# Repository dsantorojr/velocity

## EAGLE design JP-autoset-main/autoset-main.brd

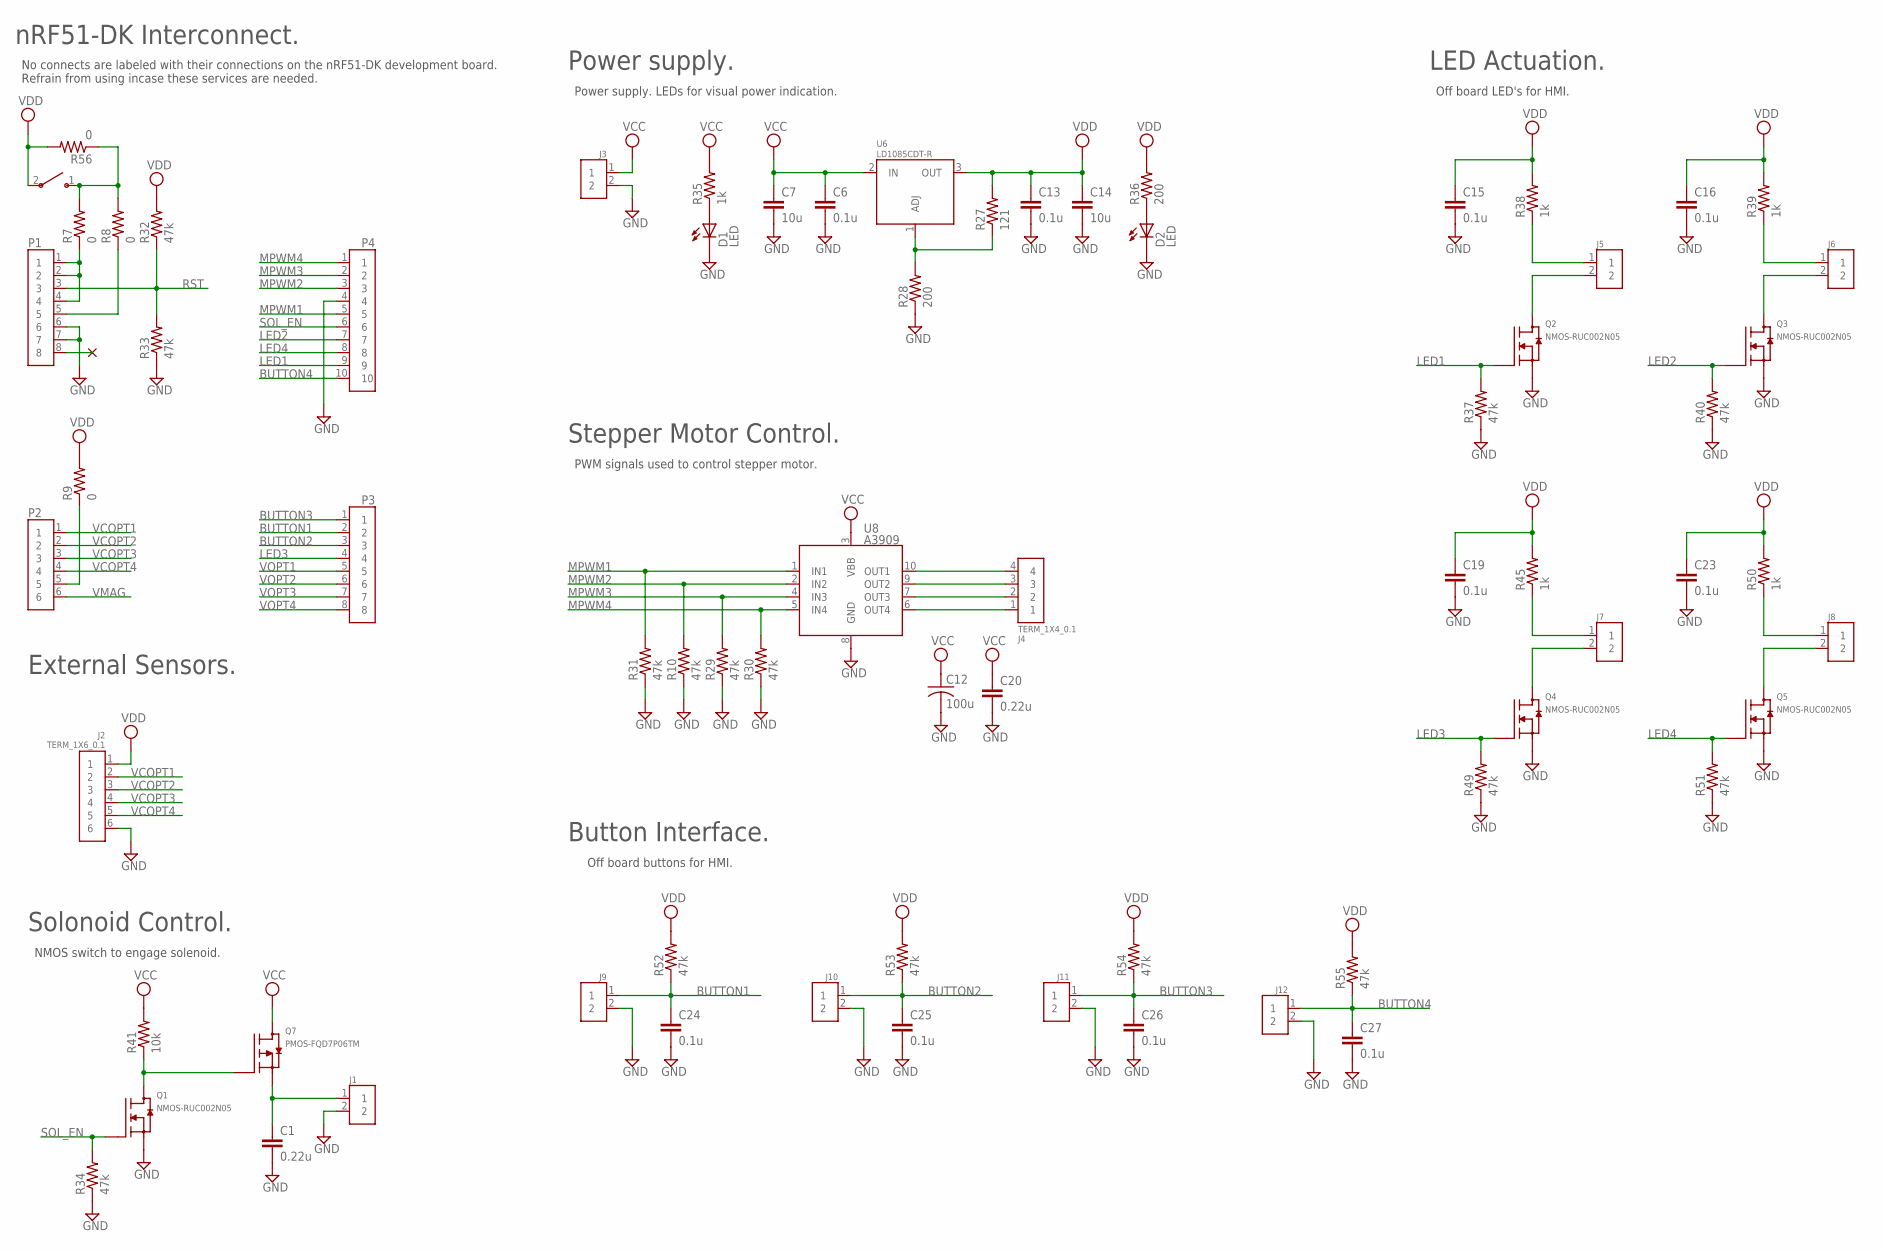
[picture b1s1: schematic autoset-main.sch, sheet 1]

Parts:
C1, C20: 0.22u; C0603
C6, C13, C15, C16, C19, C23, C24, C25, C26, C27: 0.1u; C0603
C7, C14: 10u; C0603
C12: 100u; CPOL-3.5MM
D1, D2: LED; L0805
J1, J3, J5, J6, J7, J8, J9, J10, J11, J12: TERM_1X2_0.1
J2: TERM_1X6_0.1
J4: TERM_1X4_0.1
P1, P3: RECT_1X8; RECT_1X8_0.1
P2: RECT_1X6; RECT_1X6_0.1
P4: RECT_1X10; RECT_1X10_0.1
Q1, Q2, Q3, Q4, Q5: NMOS-RUC002N05; SOT23
Q7: PMOS-FQD7P06TM; TO252
R7, R8, R9, R56: 0; R0603
R10, R29, R30, R31, R32, R33, R34, R37, R40, R49, R51, R52, R53, R54, R55: 47k; R0603
R27: 121; R0603
R28, R36: 200; R0603
R35, R38, R39, R45, R50: 1k; R0603
R41: 10k; R0603
SW1: GPTS203211B
U6: LD1085CDT-R; TO252
U8: A3909; SSOP10
Z15: NC; NC_TH

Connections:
BUTTON1: C24.1, J9.1, P3.2, R52.1
BUTTON2: C25.1, J10.1, P3.3, R53.1
BUTTON3: C26.1, J11.1, P3.1, R54.1
BUTTON4: C27.1, J12.1, P4.10, R55.1
GND: C1.2, C6.2, C7.2, C12.P$2 (2), C13.2, C14.2, C15.2, C16.2, C19.2, C20.2, C23.2, C24.2, C25.2, C26.2, C27.2, D1.2 (C), D2.2 (C), J1.2, J2.6, J3.2, J9.2, J10.2, J11.2, J12.2, P1.6, P1.7, P4.4, Q1.1 (S), Q2.1 (S), Q3.1 (S), Q4.1 (S), Q5.1 (S), R10.1, R28.1, R29.1, R30.1, R31.1, R33.1, R34.1, R37.1, R40.1, R49.1, R51.1, U8.8 (GND); also elsewhere on the board
LED1: P4.9, Q2.2 (G), R37.2
LED2: P4.7, Q3.2 (G), R40.2
LED3: P3.4, Q4.2 (G), R49.2
LED4: P4.8, Q5.2 (G), R51.2
MPWM1: P4.5, R31.2, U8.1 (IN1)
MPWM2: P4.3, R10.2, U8.2 (IN2)
MPWM3: P4.2, R29.2, U8.4 (IN3)
MPWM4: P4.1, R30.2, U8.5 (IN4)
unnamed: P1.8, Z15.P$1
unnamed: J6.2, Q3.3 (D)
unnamed: R7.2, R8.2, R56.1, SW1.1
unnamed: P1.1, P1.2, P1.4, R7.1
unnamed: J4.4, U8.10 (OUT1)
unnamed: R27.1, R28.2, U6.1 (ADJ)
unnamed: J4.3, U8.9 (OUT2)
unnamed: J5.2, Q2.3 (D)
unnamed: J5.1, R38.1
unnamed: J6.1, R39.1
unnamed: J7.2, Q4.3 (D)
unnamed: J7.1, R45.1
unnamed: J8.2, Q5.3 (D)
unnamed: J4.2, U8.7 (OUT3)
unnamed: J4.1, U8.6 (OUT4)
unnamed: J8.1, R50.1
unnamed: P2.5, R9.1
unnamed: C1.1, J1.1, Q7.3 (D)
unnamed: P1.5, R8.1
unnamed: Q1.3 (D), Q7.1 (G), R41.1
unnamed: D1.1 (A), R35.1
unnamed: D2.1 (A), R36.1
RST: P1.3, R32.1, R33.2
SOL_EN: P4.6, Q1.2 (G), R34.2
VCC: C6.1, C7.1, C12.P$1 (1), C20.1, J3.1, Q7.2 (S), R35.2, R41.2, U6.2 (IN), U8.3 (VBB)
VCOPT1: J2.2, P2.1
VCOPT2: J2.3, P2.2
VCOPT3: J2.4, P2.3
VCOPT4: J2.5, P2.4
VDD: C13.1, C14.1, C15.1, C16.1, C19.1, C23.1, J2.1, R9.2, R27.2, R32.2, R36.2, R38.2, R39.2, R45.2, R50.2, R52.2, R53.2, R54.2, R55.2, R56.2, SW1.2, U6.3 (OUT); also elsewhere on the board
VMAG: P2.6; also elsewhere on the board
VOPT1: P3.5; also elsewhere on the board
VOPT2: P3.6; also elsewhere on the board
VOPT3: P3.7; also elsewhere on the board
VOPT4: P3.8; also elsewhere on the board

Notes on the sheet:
nRF51-DK Interconnect.
No connects are labeled with their connections on the nRF51-DK development board. Refrain from using incase these services are needed.
Power supply.
Power supply. LEDs for visual power indication.
Solonoid Control.
NMOS switch to engage solenoid.
Stepper Motor Control.
PWM signals used to control stepper motor.
External Sensors.
LED Actuation.
Off board LED's for HMI.
Button Interface.
Off board buttons for HMI.

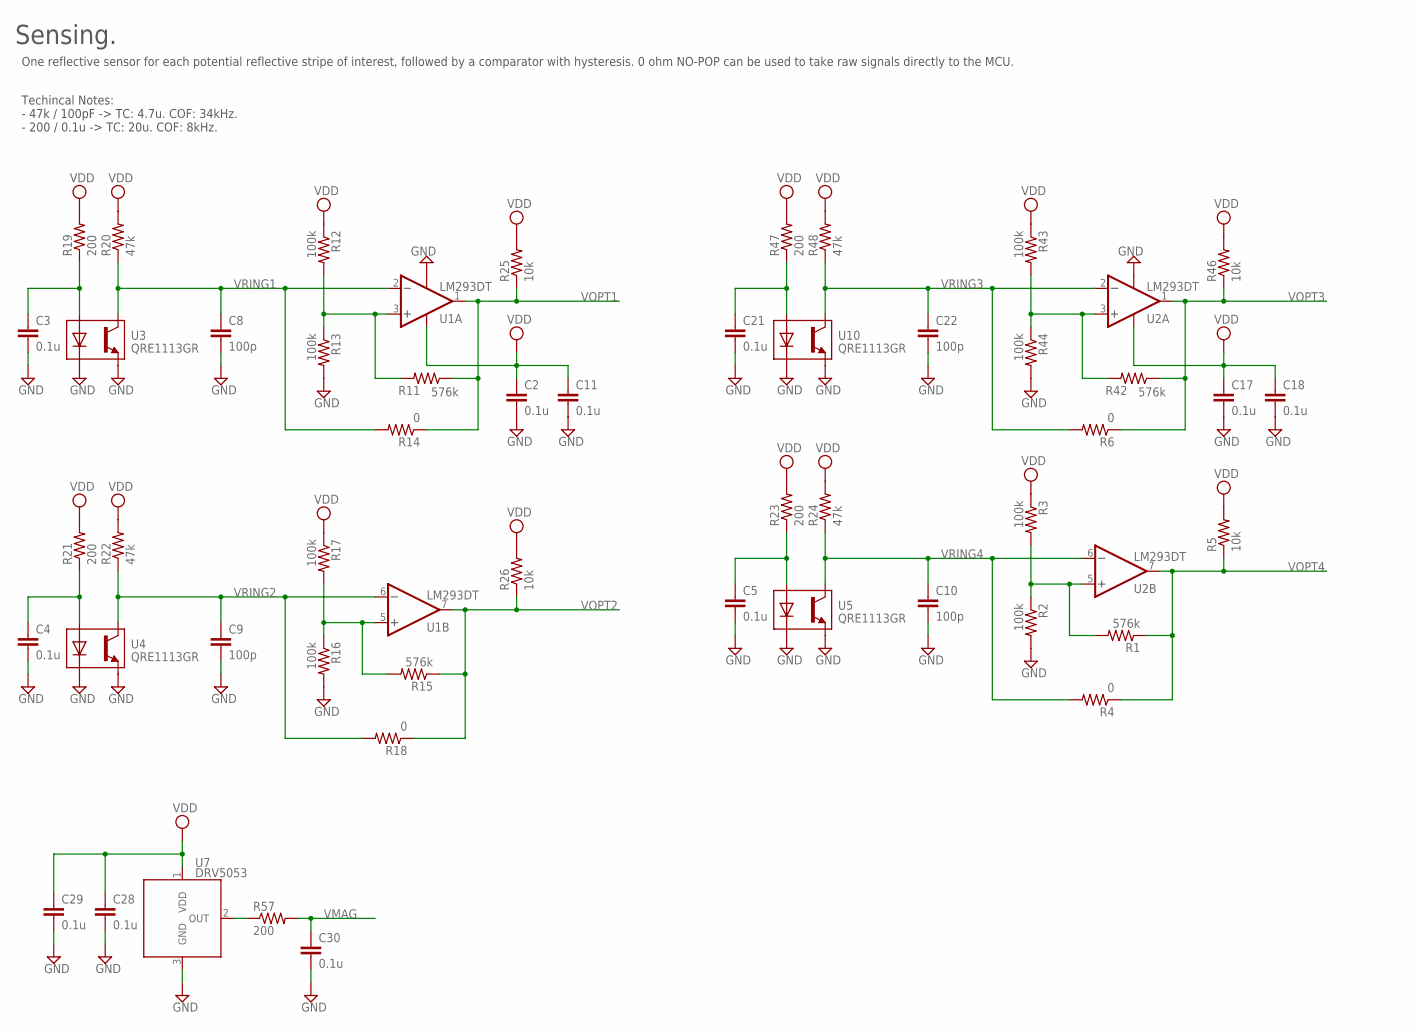
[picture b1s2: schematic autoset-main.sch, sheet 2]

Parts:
C2, C3, C4, C5, C11, C17, C18, C21, C28, C29, C30: 0.1u; C0603
C8, C9, C10, C22: 100p; C0603
R1, R11, R15, R42: 576k; R0603
R2, R3, R12, R13, R16, R17, R43, R44: 100k; R0603
R4, R6, R14, R18: 0; R0603
R5, R25, R26, R46: 10k; R0603
R19, R21, R23, R47, R57: 200; R0603
R20, R22, R24, R48: 47k; R0603
U1, U2: LM293DT; SOIC8
U3, U4, U5, U10: QRE1113GR; REFL
U7: DRV5053; SOT23

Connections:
GND: C2.2, C3.2, C4.2, C5.2, C8.2, C9.2, C10.2, C11.2, C17.2, C18.2, C21.2, C22.2, C28.2, C29.2, C30.2, R2.2, R13.2, R16.2, R44.2, U1.4 (V-), U2.4 (V-), U3.2 (DC), U3.4 (E), U4.2 (DC), U4.4 (E), U5.2 (DC), U5.4 (E), U7.3 (GND), U10.2 (DC), U10.4 (E); also elsewhere on the board
unnamed: R1.2, R2.1, R3.2, U2.5 (+IN)
unnamed: R42.2, R43.2, R44.1, U2.3 (+IN)
unnamed: R11.2, R12.2, R13.1, U1.3 (+IN)
unnamed: C3.1, R19.1, U3.1 (DA)
unnamed: R15.2, R16.1, R17.2, U1.5 (+IN)
unnamed: C4.1, R21.1, U4.1 (DA)
unnamed: C5.1, R23.1, U5.1 (DA)
unnamed: R57.1, U7.2 (OUT)
unnamed: C21.1, R47.1, U10.1 (DA)
VDD: C2.1, C11.1, C17.1, C18.1, C28.1, C29.1, R3.1, R5.2, R12.1, R17.1, R19.2, R20.2, R21.2, R22.2, R23.2, R24.2, R25.2, R26.2, R43.1, R46.2, R47.2, R48.2, U1.8 (V+), U2.8 (V+), U7.1 (VDD); also elsewhere on the board
VMAG: C30.1, R57.2; also elsewhere on the board
VOPT1: R11.1, R14.1, R25.1, U1.1 (OUT); also elsewhere on the board
VOPT2: R15.1, R18.1, R26.1, U1.7 (OUT); also elsewhere on the board
VOPT3: R6.1, R42.1, R46.1, U2.1 (OUT); also elsewhere on the board
VOPT4: R1.1, R4.1, R5.1, U2.7 (OUT); also elsewhere on the board
VRING1: C8.1, R14.2, R20.1, U1.2 (-IN), U3.3 (C)
VRING2: C9.1, R18.2, R22.1, U1.6 (-IN), U4.3 (C)
VRING3: C22.1, R6.2, R48.1, U2.2 (-IN), U10.3 (C)
VRING4: C10.1, R4.2, R24.1, U2.6 (-IN), U5.3 (C)

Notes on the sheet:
Sensing.
One reflective sensor for each potential reflective stripe of interest, followed by a comparator with hysteresis. 0 ohm NO-POP can be used to take raw signals directly to the MCU.
Techincal Notes: - 47k / 100pF -> TC: 4.7u. COF: 34kHz. - 200 / 0.1u -> TC: 20u. COF: 8kHz.

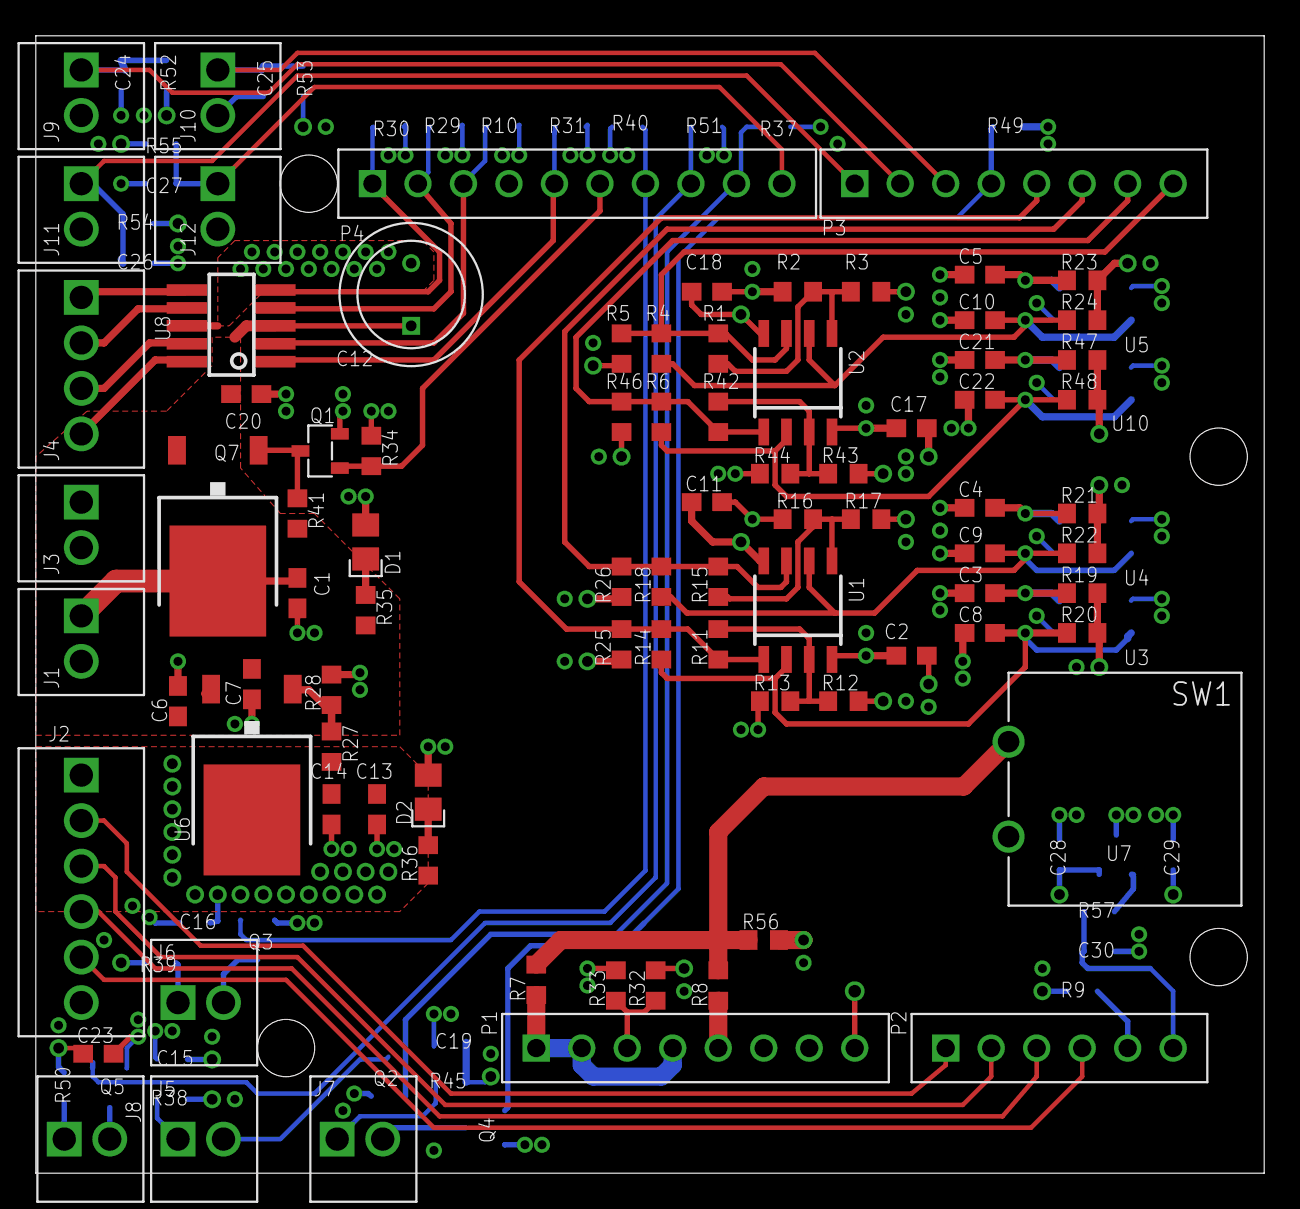
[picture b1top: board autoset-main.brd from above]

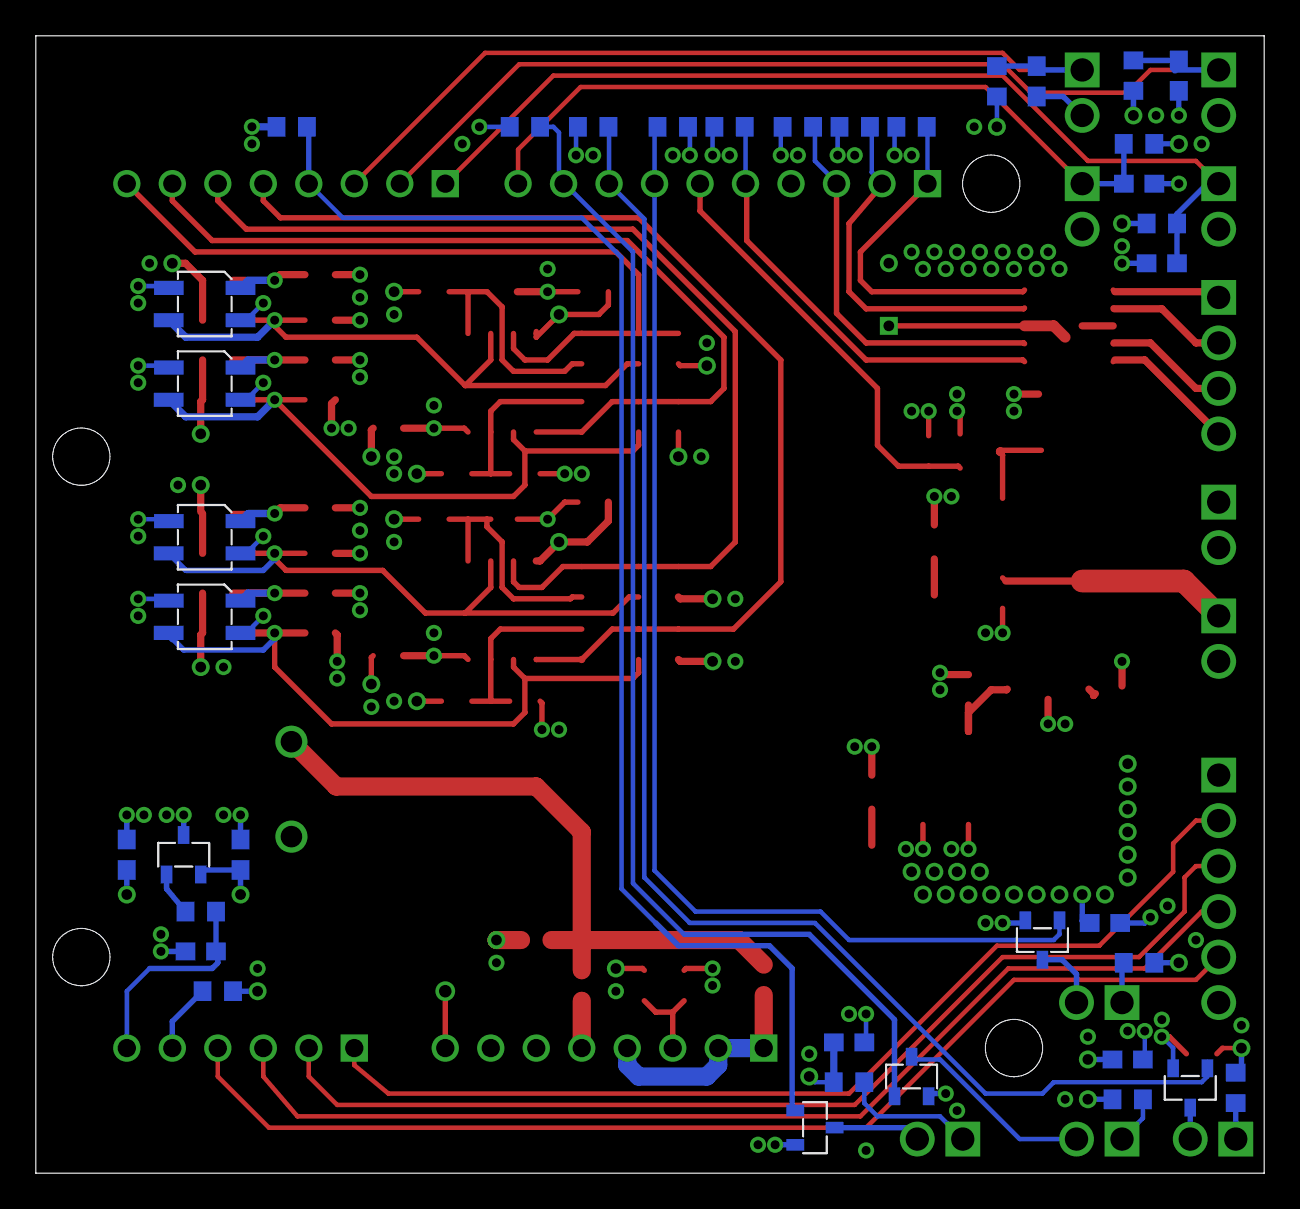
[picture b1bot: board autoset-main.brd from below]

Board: 4 copper layers, 68.6 x 63.5 mm, 122 parts (37 on the bottom side), 61 nets.

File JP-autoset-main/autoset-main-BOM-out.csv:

Qty,Value,Device,Package,Parts,Description,DKPN,,
8,0,R0603,R0603,R4; R6; R7; R8; R9; R14; R18; R56,,541-2779-1-ND,,
21,0.1u,C0603,C0603,C2; C3; C4; C5; C6; C11; C13; C15; C16; C17; C18; C19; C21; C23; C24; C25; C26; C27; C28; C29; C30,,490-1519-1-ND,,
2,0.22u,C0603,C0603,C1; C20,,490-8017-1-ND,,
8,100k,R0603,R0603,R2; R3; R12; R13; R16; R17; R43; R44,,RHM100KDCT-ND,,
4,100p,C0603,C0603,C8; C9; C10; C22,,490-4767-1-ND,,
1,100u,C-POL3.5MM,CPOL-3.5MM,C12,,493-10432-1-ND,,
5,10k,R0603,R0603,R5; R25; R26; R41; R46,,RHM10KDCT-ND,,
2,10u,C0603,C0603,C7; C14,,490-7202-1-ND,,
1,121,R0603,R0603,R27,,311-121HRCT-ND,,
5,1k,R0603,R0603,R35; R38; R39; R45; R50,,RHM1.0KDCT-ND,,
7,200,R0603,R0603,R19; R21; R23; R28; R36; R47; R57,,RHM200DCT-ND,,
19,47k,R0603,R0603,R10; R20; R22; R24; R29; R30; R31; R32; R33; R34; R37; R40; R48; R49; R51; R52; R53; R54; R55,,RHM47KDCT-ND,,
4,576k,R0603,R0603,R1; R11; R15; R42,,311-576KHRCT-ND,,
1,A3909,A3909,SSOP10,U8,,620-1498-1-ND,,
1,DRV5053,DRV5053,SOT23,U7,,296-38460-1-ND,,
1,GPTS203211B,GPTS203211B,GPTS203211B,SW1,,CW181-ND,,
1,LD1085CDT-R,LD1085CDT-R,TO252,U6,,497-3418-1-ND,,
1,LED,LED,L0805,D2,,475-1410-1-ND,,
1,LED,LED,L0805,D1,,475-1415-1-ND,,
2,LM293DT,LM293DT,SOIC8,U1; U2,,497-1566-1-ND,,
1,NC,NC,NC_TH,Z15,,,,
5,NMOS-RUC002N05,NMOS-RUC002N05,SOT23,Q1; Q2; Q3; Q4; Q5,,RUC002N05T116CT-ND,,
1,PMOS-FQD7P06TM,PMOS-FQD7P06TM,TO252,Q7,,FQD7P06TMCT-ND,,
4,QRE1113GR,QRE1113GR,REFL,U3; U4; U5; U10,,QRE1113GRCT-ND,,
1,RECT_1X10,RECT_1X10,RECT_1X10_0.1,P4,,S1011EC-10-ND,,
1,RECT_1X6,RECT_1X6,RECT_1X6_0.1,P2,,S1011EC-06-ND,,
2,RECT_1X8,RECT_1X8,RECT_1X8_0.1,P1; P3,,S1011EC-08-ND,,
10,TERM_1X2_0.1,TERM_1X2_0.1,TERM_1X2_0.1,J1; J3; J5; J6; J7; J8; J9; J10; J11; J12,,ED10561-ND,,
1,TERM_1X4_0.1,TERM_1X4_0.1,TERM_1X4_0.1,J4,,ED10563-ND,,
1,TERM_1X6_0.1,TERM_1X6_0.1,TERM_1X6_0.1,J2,,ED10565-ND,,

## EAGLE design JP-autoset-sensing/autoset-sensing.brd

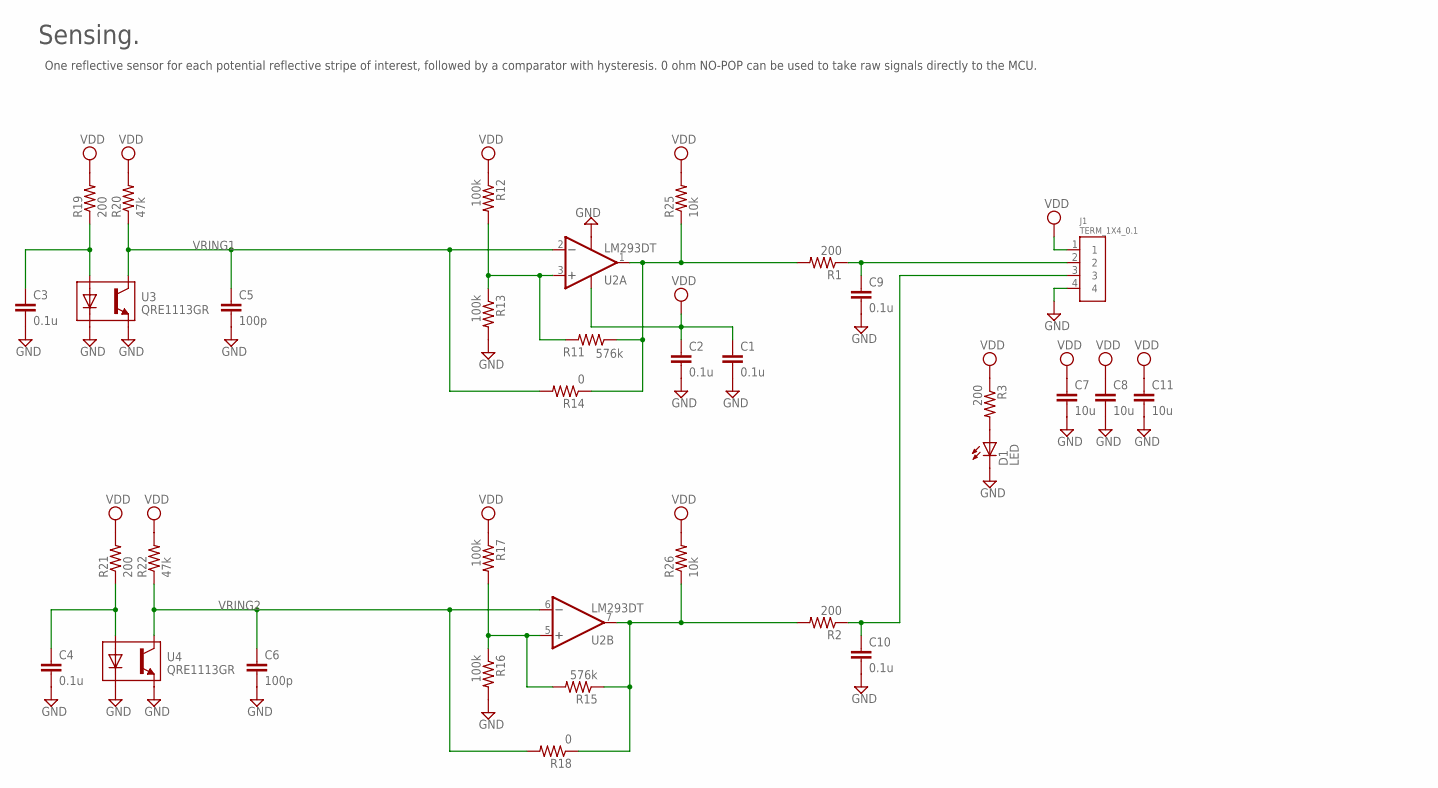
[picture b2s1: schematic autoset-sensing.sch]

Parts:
C1, C2, C3, C4, C9, C10: 0.1u; C0603
C5, C6: 100p; C0603
C7, C8, C11: 10u; C0603
D1: LED; L0805
J1: TERM_1X4_0.1
R1, R2, R3, R19, R21: 200; R0603
R11, R15: 576k; R0603
R12, R13, R16, R17: 100k; R0603
R14, R18: 0; R0603
R20, R22: 47k; R0603
R25, R26: 10k; R0603
U2: LM293DT; SOIC8
U3, U4: QRE1113GR; REFL

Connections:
GND: C1.2, C2.2, C3.2, C4.2, C5.2, C6.2, C7.2, C8.2, C9.2, C10.2, C11.2, D1.2 (C), J1.4, R13.2, R16.2, U2.4 (V-), U3.2 (DC), U3.4 (E), U4.2 (DC), U4.4 (E)
unnamed: C9.1, J1.2, R1.1
unnamed: C10.1, J1.3, R2.1
unnamed: D1.1 (A), R3.2
unnamed: R11.2, R12.2, R13.1, U2.3 (+IN)
unnamed: R1.2, R11.1, R14.1, R25.1, U2.1 (OUT)
unnamed: C3.1, R19.1, U3.1 (DA)
unnamed: R15.2, R16.1, R17.2, U2.5 (+IN)
unnamed: R2.2, R15.1, R18.1, R26.1, U2.7 (OUT)
unnamed: C4.1, R21.1, U4.1 (DA)
VDD: C1.1, C2.1, C7.1, C8.1, C11.1, J1.1, R3.1, R12.1, R17.1, R19.2, R20.2, R21.2, R22.2, R25.2, R26.2, U2.8 (V+)
VRING1: C5.1, R14.2, R20.1, U2.2 (-IN), U3.3 (C)
VRING2: C6.1, R18.2, R22.1, U2.6 (-IN), U4.3 (C)

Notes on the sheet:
Sensing.
One reflective sensor for each potential reflective stripe of interest, followed by a comparator with hysteresis. 0 ohm NO-POP can be used to take raw signals directly to the MCU.

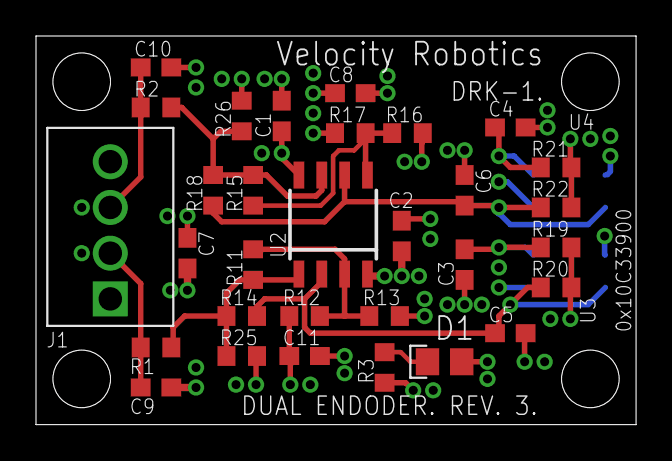
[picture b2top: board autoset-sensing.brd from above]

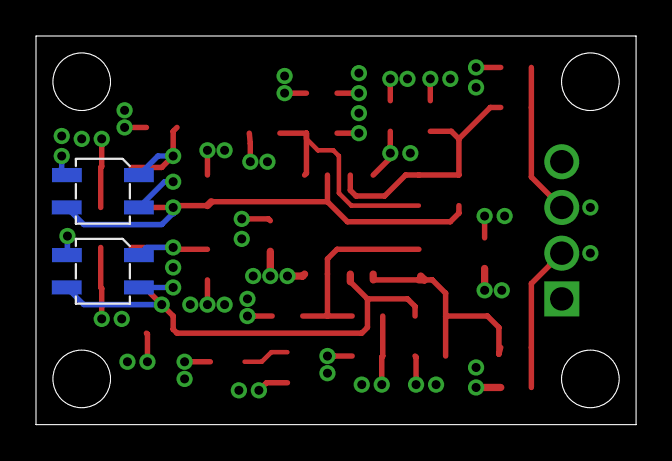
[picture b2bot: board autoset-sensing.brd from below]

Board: 4 copper layers, 33.3 x 21.6 mm, 33 parts (2 on the bottom side), 13 nets.

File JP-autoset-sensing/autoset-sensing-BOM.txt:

Partlist exported from /Users/danielsantoro/Documents/eagle/velocity/JP-autoset-sensing/autoset-sensing.sch at 11/14/16 1:10 AM

Qty Value        Device       Package      Parts              Description DKPN           
2   0            R0603        R0603        R14, R18                       541-2779-1-ND  
4   0.1u         C0603        C0603        C1, C2, C3, C4                 490-1519-1-ND  
4   100k         R0603        R0603        R12, R13, R16, R17             RHM100KDCT-ND  
2   100p         C0603        C0603        C5, C6                         490-4767-1-ND  
2   10k          R0603        R0603        R25, R26                       RHM10KDCT-ND   
2   200          R0603        R0603        R19, R21                       RHM200DCT-ND   
2   47k          R0603        R0603        R20, R22                       RHM47KDCT-ND   
2   576k         R0603        R0603        R11, R15                       311-576KHRCT-ND
1   LM293DT      LM293DT      SOIC8        U2                             497-1566-1-ND  
2   QRE1113GR    QRE1113GR    REFL         U3, U4                         QRE1113GRCT-ND 
1   TERM_1X4_0.1 TERM_1X4_0.1 TERM_1X4_0.1 J1                             ED10563-ND

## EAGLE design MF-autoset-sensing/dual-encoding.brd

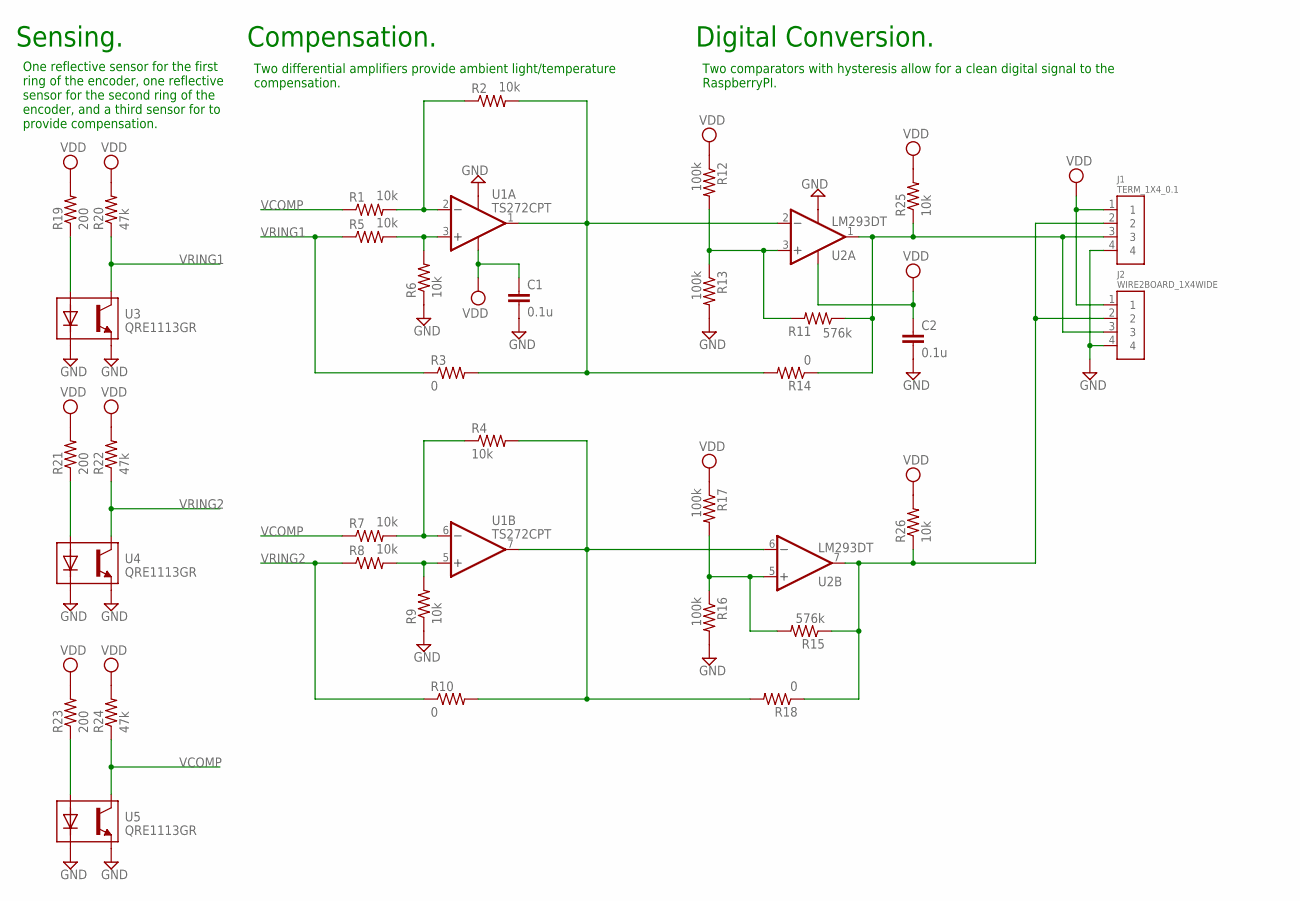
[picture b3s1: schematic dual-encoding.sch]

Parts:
C1, C2: 0.1u; C0805
J1: TERM_1X4_0.1
J2: WIRE2BOARD_1X4WIDE; WIRE2BOARD_1X4W
R1, R2, R4, R5, R6, R7, R8, R9, R25, R26: 10k; R0805
R3, R10, R14, R18: 0; R0805
R11, R15: 576k; R0805
R12, R13, R16, R17: 100k; R0805
R19, R21, R23: 200; R0805
R20, R22, R24: 47k; R0805
U1: TS272CPT; TSSOP8
U2: LM293DT; SOIC8
U3, U4, U5: QRE1113GR; REFL

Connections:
GND: C1.2, C2.2, J1.4, J2.4, R6.1, R9.1, R13.2, R16.2, U1.4 (V-), U2.4 (V-), U3.2 (DC), U3.4 (E), U4.2 (DC), U4.4 (E), U5.2 (DC), U5.4 (E)
unnamed: R5.2, R6.2, U1.3 (+IN)
unnamed: R1.2, R2.1, U1.2 (-IN)
unnamed: R2.2, R3.2, R14.2, U1.1 (OUT), U2.2 (-IN)
unnamed: R4.1, R7.2, U1.6 (-IN)
unnamed: R4.2, R10.2, R18.2, U1.7 (OUT), U2.6 (-IN)
unnamed: R8.2, R9.2, U1.5 (+IN)
unnamed: R11.2, R12.2, R13.1, U2.3 (+IN)
unnamed: J1.3, J2.3, R11.1, R14.1, R25.1, U2.1 (OUT)
unnamed: R19.1, U3.1 (DA)
unnamed: R15.2, R16.1, R17.2, U2.5 (+IN)
unnamed: J1.2, J2.2, R15.1, R18.1, R26.1, U2.7 (OUT)
unnamed: R21.1, U4.1 (DA)
unnamed: R23.1, U5.1 (DA)
VCOMP: R1.1, R7.1, R24.1, U5.3 (C)
VDD: C1.1, C2.1, J1.1, J2.1, R12.1, R17.1, R19.2, R20.2, R21.2, R22.2, R23.2, R24.2, R25.2, R26.2, U1.8 (V+), U2.8 (V+)
VRING1: R3.1, R5.1, R20.1, U3.3 (C)
VRING2: R8.1, R10.1, R22.1, U4.3 (C)

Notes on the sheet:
Sensing.
Compensation.
Two differential amplifiers provide ambient light/temperature compensation.
One reflective sensor for the first ring of the encoder, one reflective sensor for the second ring of the encoder, and a third sensor for to provide compensation.
Digital Conversion.
Two comparators with hysteresis allow for a clean digital signal to the RaspberryPI.

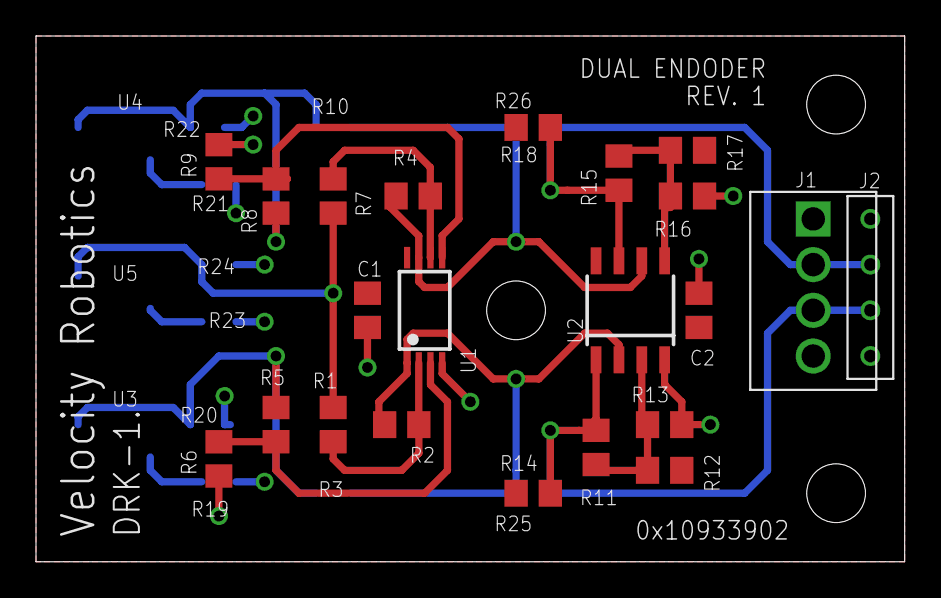
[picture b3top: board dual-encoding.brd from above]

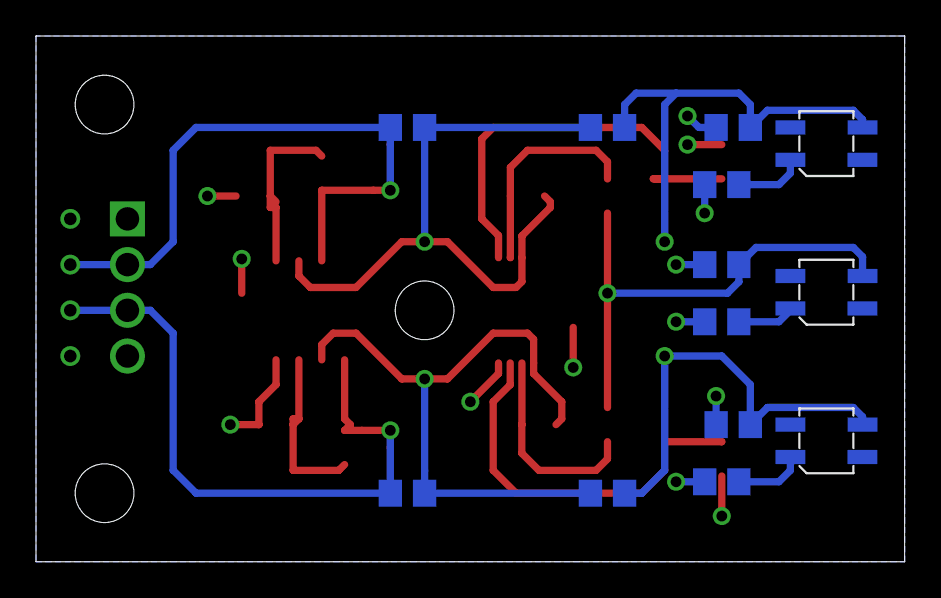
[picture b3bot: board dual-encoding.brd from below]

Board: 2 copper layers, 48.3 x 29.2 mm, 35 parts (13 on the bottom side), 18 nets.

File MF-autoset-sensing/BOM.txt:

Partlist exported from /Users/danielsantoro/Documents/eagle/velocity/dual-encoding/dual-encoding.sch at 9/14/16 1:05 AM

Qty Value              Device             Package         Parts                          Description DKPN            
4   0                  R                  R0805           R3, R10, R14, R18                          311-0.0ARCT-ND X
2   0.1u               C0805              C0805           C1, C2                                     1276-6468-1-ND X
4   100k               R                  R0805           R12, R13, R16, R17                         311-100KCRCT-ND X
8   10k                R                  R0805           R1, R2, R4, R5, R6, R7, R8, R9             311-10.0KCRCT-ND X
3   200                R                  R0805           R19, R21, R23                              311-200ARCT-ND X
3   47k                R                  R0805           R20, R22, R24                              311-47KARCT-ND X
2   576k               R                  R0805           R11, R15                                   311-576KCRCT-ND X
1   LM293DT            LM293DT            SOIC8           U2                                         497-1566-1-ND X  
3   QRE1113GR          QRE1113GR          REFL            U3, U4, U5                                 QRE1113GRCT-ND X
1   TERM_1X4_0.1       TERM_1X4_0.1       TERM_1X4_0.1    J1                                         ED10563-ND X    
1   TS272CPT           TS272CPT           TSSOP8          U1                                         497-8079-1-ND X
1   WIRE2BOARD_1X4WIDE WIRE2BOARD_1X4WIDE WIRE2BOARD_1X4W J2

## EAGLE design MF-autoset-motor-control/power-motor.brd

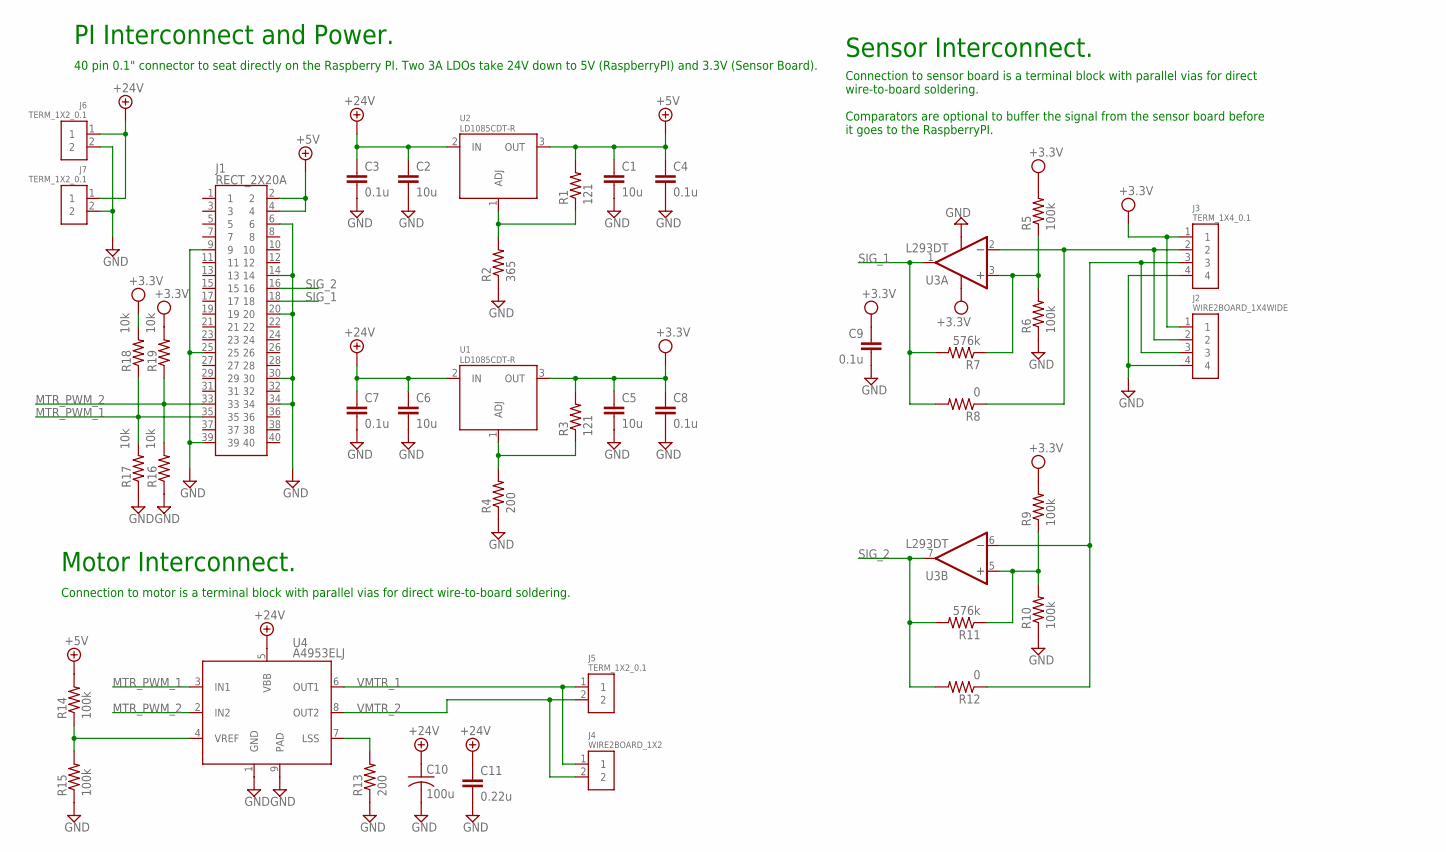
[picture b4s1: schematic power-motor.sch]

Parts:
C1, C2, C5, C6: 10u; C0805
C3, C4, C7, C8, C9: 0.1u; C0805
C10: 100u; CPOL-8
C11: 0.22u; C0805
J1: RECT_2X20A; RECT_2X20_0.1
J2: WIRE2BOARD_1X4WIDE; WIRE2BOARD_1X4W
J3: TERM_1X4_0.1
J4: WIRE2BOARD_1X2
J5, J6, J7: TERM_1X2_0.1
R1, R3: 121; R0805
R2: 365; R0805
R4: 200; R0805
R5, R6, R9, R10, R14, R15: 100k; R0805
R7, R11: 576k; R0805
R8, R12: 0; R0805
R13: 200; R2512
R16, R17, R18, R19: 10k; R0805
U1, U2: LD1085CDT-R; TO252
U3: L293DT; SOIC8
U4: A4953ELJ; SOIC8

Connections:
+5V: C1.1, C4.1, J1.2, J1.4, R1.2, R14.2, U2.3 (OUT)
+24V: C2.1, C3.1, C6.1, C7.1, C10.P$1 (1), C11.1, J6.1, J7.1, U1.2 (IN), U2.2 (IN), U4.5 (VBB)
GND: C1.2, C2.2, C3.2, C4.2, C5.2, C6.2, C7.2, C8.2, C9.2, C10.P$2 (2), C11.2, J1.6, J1.9, J1.14, J1.20, J1.25, J1.30, J1.34, J1.39, J2.4, J3.4, J6.2, J7.2, R2.1, R4.1, R6.1, R10.1, R13.1, R15.1, R16.1, R17.1, U3.4 (V-), U4.1 (GND), U4.9 (PAD)
MTR_PWM_1: J1.35, R17.2, R18.1, U4.3 (IN1)
MTR_PWM_2: J1.33, R16.2, R19.1, U4.2 (IN2)
unnamed: R5.1, R6.2, R7.1, U3.3 (+IN)
unnamed: R1.1, R2.2, U2.1 (ADJ)
unnamed: J2.2, J3.2, R8.1, U3.2 (-IN)
unnamed: J2.3, J3.3, R12.1, U3.6 (-IN)
unnamed: R3.1, R4.2, U1.1 (ADJ)
unnamed: R14.1, R15.2, U4.4 (VREF)
unnamed: R13.2, U4.7 (LSS)
unnamed: R9.1, R10.2, R11.1, U3.5 (+IN)
SIG_1: J1.18, R7.2, R8.2, U3.1 (OUT)
SIG_2: J1.16, R11.2, R12.2, U3.7 (OUT)
VDD: C5.1, C8.1, C9.1, J2.1, J3.1, R3.2, R5.2, R9.2, R18.2, R19.2, U1.3 (OUT), U3.8 (V+)
VMTR_1: J4.1, J5.1, U4.6 (OUT1)
VMTR_2: J4.2, J5.2, U4.8 (OUT2)

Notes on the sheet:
Sensor Interconnect.
Connection to sensor board is a terminal block with parallel vias for direct wire-to-board soldering. Comparators are optional to buffer the signal from the sensor board before it goes to the RaspberryPI.
Motor Interconnect.
Connection to motor is a terminal block with parallel vias for direct wire-to-board soldering.
PI Interconnect and Power.
40 pin 0.1" connector to seat directly on the Raspberry PI. Two 3A LDOs take 24V down to 5V (RaspberryPI) and 3.3V (Sensor Board).
